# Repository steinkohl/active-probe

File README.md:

# active-probe
2GHz active FET probe build around the BUF802.
Schematic is copied from https://github.com/jmwilson/oshw-active-probe

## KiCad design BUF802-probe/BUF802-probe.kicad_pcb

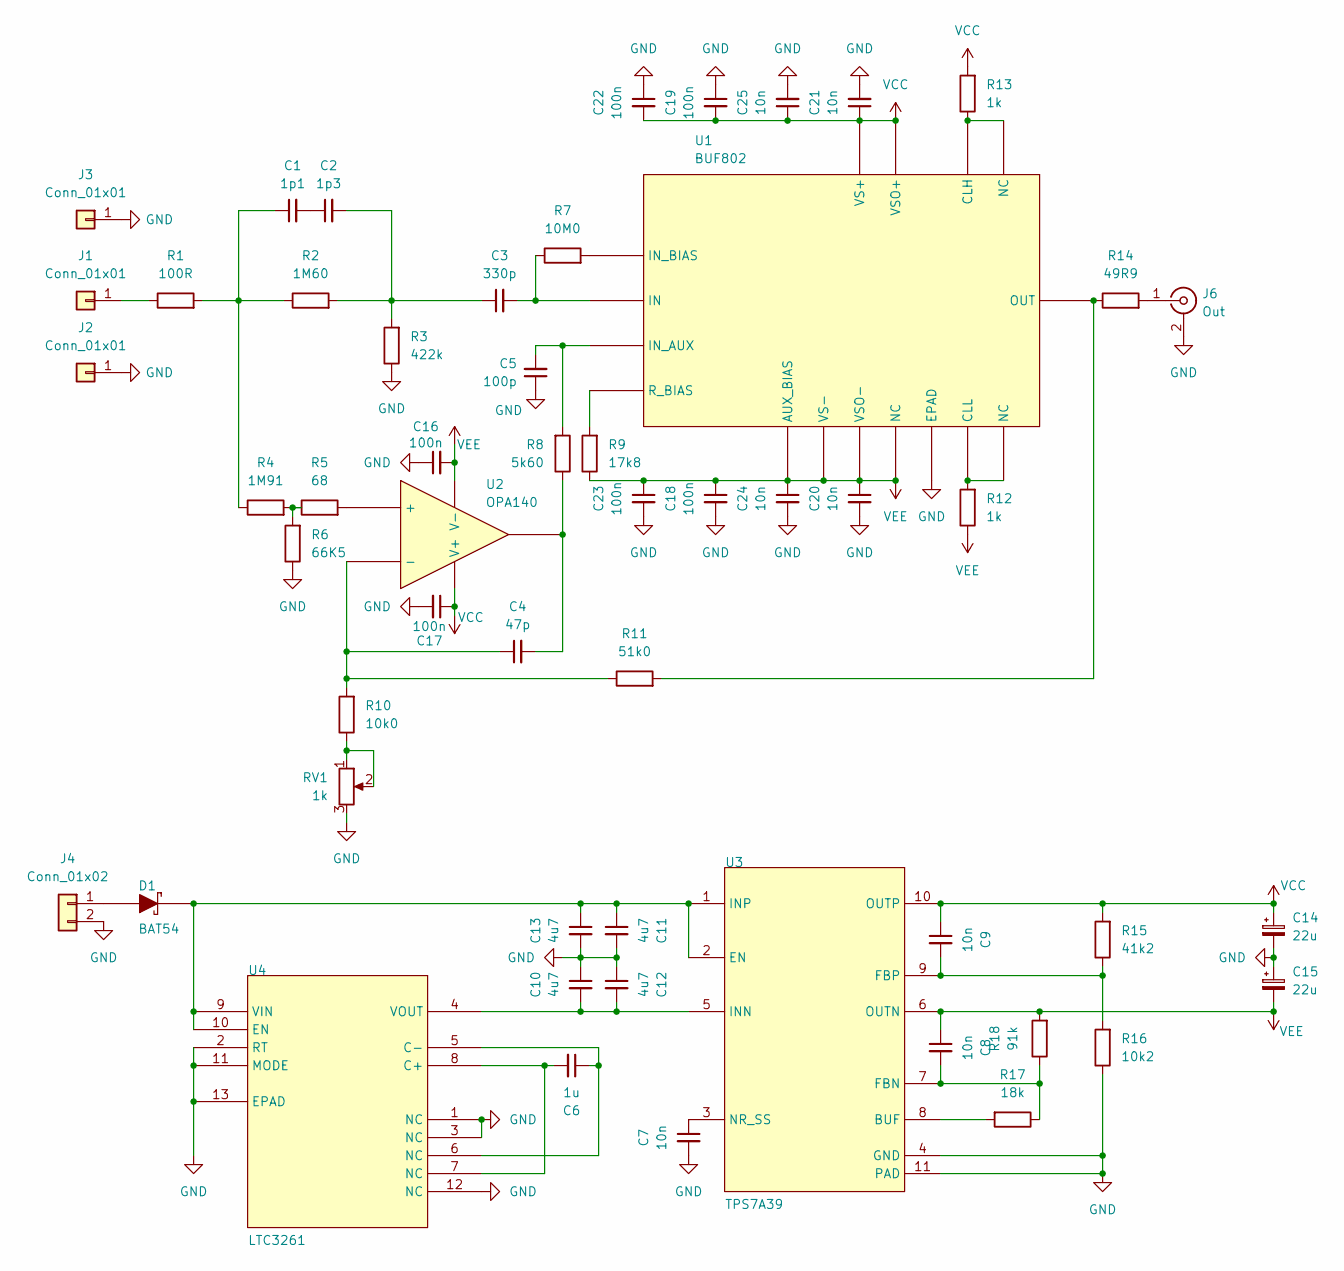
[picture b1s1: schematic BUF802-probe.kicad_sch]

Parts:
C1: 1p1; C_0402_1005Metric
C2: 1p3; C_0402_1005Metric
C3: 330p; C_0402_1005Metric
C4: 47p; C_0402_1005Metric
C5: 100p; C_0402_1005Metric
C6: 1u; C_0805_2012Metric; PartNr CC0805KKX7R9BB105
C7, C8, C9: 10n; C_0402_1005Metric; PartNr GRM1555C1E103JE01D
C10, C11, C12, C13: 4u7; C_0805_2012Metric; PartNr GRM21BZ71H475KE15K
C14, C15: 22u; CP_EIA-3528-21_Kemet-B; PartNr T491B226K016AT
C16, C17: 100n; C_0603_1608Metric; PartNr CC0603KRX7R9BB104
C18, C19, C22, C23: 100n; CAPC0816X55N; PartNr TWK107B7104MVHT
C20, C21, C24, C25: 10n; C_0402_1005Metric; PartNr GRM155R71H103KA88D
D1: BAT54; SOT-23; MANUFACTURER PART NUMBER BAT54,215
J1, J2, J3: Conn_01x01; SolderWirePad_1x01_SMD_1x2mm
J4: Conn_01x02; SolderWire-0.25sqmm_1x02_P4.2mm_D0.65mm_OD1.7mm
J6: Out; LINX_CONSMA001-SMD-G-T
R1: 100R; R_0402_1005Metric
R2: 1M60; R_0402_1005Metric
R3: 422k; R_0402_1005Metric
R4: 1M91; R_0402_1005Metric
R5: 68; R_0402_1005Metric
R6: 66K5; R_0402_1005Metric
R7: 10M0; R_0402_1005Metric
R8: 5k60; R_0402_1005Metric
R9: 17k8; R_0402_1005Metric
R10: 10k0; R_0402_1005Metric
R11: 51k0; R_0402_1005Metric
R12, R13: 1k; R_0402_1005Metric
R14: 49R9; R_0402_1005Metric
R15: 41k2; R_0402_1005Metric
R16: 10k2; R_0402_1005Metric
R17: 18k; R_0402_1005Metric
R18: 91k; R_0402_1005Metric
RV1: 1k; TRIM_PVG3A
U1: BUF802; VQFN-16-1EP_3x3mm_P0.5mm_EP1.68x1.68mm; MANUFACTURER PART NUMBER BUF802IRGTR
U2: OPA140; SOIC-8_3.9x4.9mm_P1.27mm; MANUFACTURER PART NUMBER OPA140AIDR
U3: TPS7A39; Texas_DSC0010J_ThermalVias; MANUFACTURER_PART_NUMBER TPS7A3901DSCR
U4: LTC3261; MSOP-12-1EP_3x4.039mm_P0.65mm_EP1.651x2.845mm_ThermalVias; MANUFACTURER_PART_NUMBER ltc3261emse#pbf

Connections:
GND: C5.1, C7.2, C10.1, C11.2, C12.1, C13.2, C14.2, C15.1, C16.1, C17.2, C18.2, C19.1, C20.2, C21.2, C22.1, C23.2, C24.2, C25.2, J2.1, J3.1, J4.2, J6.2 (Ext), R3.1, R6.1, R16.1, RV1.3, U1.17 (EPAD), U3.4 (GND), U3.11 (PAD), U4.1 (NC), U4.2 (RT), U4.3 (NC), U4.11 (MODE), U4.12 (NC), U4.13 (EPAD)
unnamed: C1.1, R1.2, R2.1, R4.1
unnamed: C1.2, C2.1
unnamed: C2.2, C3.1, R2.2, R3.2
unnamed: D1.1 (A), J4.1
unnamed: C11.1, C13.1, D1.3 (K), U3.1 (INP), U3.2 (EN), U4.9 (VIN), U4.10 (EN)
unnamed: J1.1, R1.1
unnamed: J6.1 (In), R14.2
unnamed: R4.2, R5.1, R6.2
unnamed: R10.1, RV1.1, RV1.2
unnamed: R13.1, U1.15 (CLH), U1.16 (NC)
unnamed: R12.2, U1.13 (NC), U1.14 (CLL)
unnamed: C3.2, R7.1, U1.2 (IN)
unnamed: C5.2, R8.2, U1.4 (IN_AUX)
unnamed: R7.2, U1.3 (IN_BIAS)
unnamed: R11.2, R14.1, U1.11 (OUT)
unnamed: R9.2, U1.7 (R_BIAS)
unnamed: R5.2, U2.3 (+)
unnamed: C4.1, R10.2, R11.1, U2.2 (-)
unnamed: C4.2, R8.1, U2.6 (OUT)
unnamed: R17.2, U3.8 (BUF)
unnamed: C8.2, R17.1, R18.1, U3.7 (FBN)
unnamed: C9.2, R15.1, R16.2, U3.9 (FBP)
unnamed: C10.2, C12.2, U3.5 (INN), U4.4 (VOUT)
unnamed: C7.1, U3.3 (NR_SS)
unnamed: C6.2, U4.7 (NC), U4.8 (C+)
unnamed: C6.1, U4.5 (C-), U4.6 (NC)
VCC: C9.1, C14.1, C17.1, C19.2, C21.1, C22.2, C25.1, R13.2, R15.2, U1.1 (VS+), U1.12 (VSO+), U2.7 (V+), U3.10 (OUTP)
VEE: C8.1, C15.2, C16.2, C18.1, C20.1, C23.1, C24.1, R9.1, R12.1, R18.2, U1.5 (VS-), U1.6 (AUX_BIAS), U1.8 (VS-), U1.9 (NC), U1.10 (VSO-), U2.4 (V-), U3.6 (OUTN)

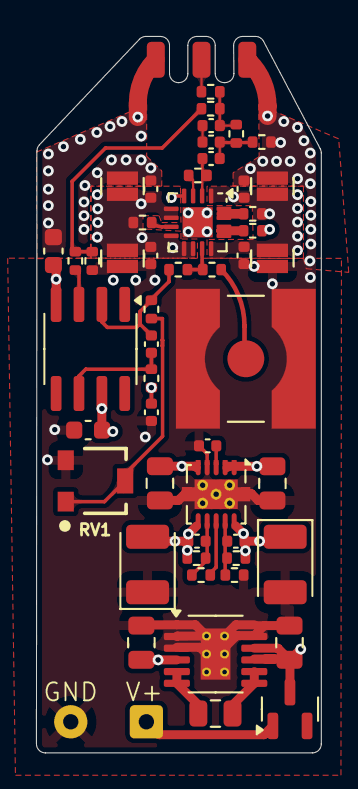
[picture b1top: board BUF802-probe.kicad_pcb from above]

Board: 4 copper layers, 15.8 x 39.8 mm, 54 parts (0 on the bottom side), 29 nets.

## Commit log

2026-05-04 first rev like orderd from aisler

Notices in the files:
parts and their libraries:
COPYRIGHT: Copyright (C) 2022 Ultra Librarian. All rights reserved.
